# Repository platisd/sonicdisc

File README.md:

# SonicDisc
A 360° ultrasonic scanner that talks over I2C using an Atmega328P and eight HC-SR04 ultrasonic sensors.

## Overview
SonicDisc is a sensor that allows you to sense your surroundings. It utilizes 8 ultrasound sensors (HC-SR04) placed at 45° angle from each other, that can measure distances from practically every direction. It can be used in hobby-grade automotive applications, e.g. autonomous driving, obstacle detection etc or wherever quickly determining surrounding distances is relevant.

The sensor transmits the collected data over I2C and uses a separate line to signal, with a short pulse, the existence of a new set of measurements. It can be mounted on top of an Arduino UNO or used standalone. Due to the nature of the HC-SR04 sensors, the measurements can be noisy, therefore it is suggested that they are filtered. A basic Arduino example that receives and filters the incoming data can be found in [examples/SonicDiscReader](examples/SonicDiscReader).

You can find the software running on the SonicDisc in [firmware/](firmware/), the PCB design in Eagle CAD format inside [hardware/](hardware/eagle) and more sample applications using the SonicDisc in [examples](examples/).

Read the story behind the module at [platis.solutions](https://platis.solutions/blog/2017/08/27/sonicdisc-360-ultrasonic-scanner/).

## How does it work
SonicDisc is comprised of an Atmega328P microcontroller that triggers all the ultrasound sensors at the same time, receives the echo pulses via pin change interrupts and then proceeds to calculate the detected distances. The use of interrupts, in contrast to how the HC-SR04 sensors are typically utilized, enable us to conduct all measurements at the "same" time which translates into new sets of `8` measurements every `10 milliseconds`.

As an I2C slave, whenever a new set of measurements is ready to be transmitted, a short pulse is sent over the `INT` pin, prompting the master to request the data. In other words the I2C master reading the data from the SonicDisc, does not have to poll but merely wait for the indicative signal and then make the I2C request. Despite not suggested, it is possible to use SonicDisc without connecting the `INT` pin to an interrupt, however the master will not be able to assure the existence of a new data.

## How to connect
| SonicDisc | Host MCU  |
| :----:    |:----:     |
| VCC       |  5V       |
| GND       |  GND      |
| SDA       |  SDA      |
| SCL       |  SCL      |
| INT       |  ISR      |

If you are mounting the SonicDisc on top of an Arduino UNO as a shield, you only have to (optionally but suggested) connect the `INT` signal to an ISR pin.

## I2C protocol
SonicDisc communicates using the I2C bus as a slave, meaning that it receives data from a master and responds to data requests.

### Address
SonicDisc's I2C address is currently hardcoded to `0x09`.

### Set operational state
SonicDisc has two operational states between which you can switch.

| **Action**                    | **Byte to send**  | **Notes**                                   |
| :-----------:                 |:-------------:    | :----:                                      |
| Set state to `STANDBY`        | 0x0A              | SonicDisc's initial state                   |
| Set state to `MEASURING`      | 0x0B              | Set to this state to start the measurements |

**Arduino example:**
```arduino
Wire.beginTransmission(0x09);
Wire.write(0x0B); // Instruct SonicDisc to start measuring
Wire.endTransmission(0x09);
```
### Get data
SonicDisc responds to I2C requests with packages of `9` bytes that include an error code and sensor measurements. A typical package structure is described below.

Regarding the error codes, when the first byte is a `0` then everything went well and the trailing measurements are valid. If it is `1`, it means that this set of data has already been transmitted and a measurement is currently under way. You will encounter this if you poll the sensor fast enough, without taking into consideration the `INT` signal which indicates SonicDisc is ready to transmit new data. Finally, `2` designates that the module is in standby state and no measurements are being conducted.

| **Byte Index** | **Range** | **Purpose** | **Notes**                                                               |
| :----:         |:----:   | :----:        | :----:                                                                  |
| 0              |  0-2    | Error code    | **0**: No error, **1**: Incomplete measurement, **2**: In standby state |
| 1              |  0-255  | Ultrasonic 0  | **0**: Error in measurement, **1**: TBD, **2-255**: Valid distance (cm) |
| 2              |  0-255  | Ultrasonic 1  | **0**: Error in measurement, **1**: TBD, **2-255**: Valid distance (cm) |
| 3              |  0-255  | Ultrasonic 2  | **0**: Error in measurement, **1**: TBD, **2-255**: Valid distance (cm) |
| 4              |  0-255  | Ultrasonic 3  | **0**: Error in measurement, **1**: TBD, **2-255**: Valid distance (cm) |
| 5              |  0-255  | Ultrasonic 4  | **0**: Error in measurement, **1**: TBD, **2-255**: Valid distance (cm) |
| 6              |  0-255  | Ultrasonic 5  | **0**: Error in measurement, **1**: TBD, **2-255**: Valid distance (cm) |
| 7              |  0-255  | Ultrasonic 6  | **0**: Error in measurement, **1**: TBD, **2-255**: Valid distance (cm) |
| 8              |  0-255  | Ultrasonic 7  | **0**: Error in measurement, **1**: TBD, **2-255**: Valid distance (cm) |

**Arduino example:**

```arduino
const unsigned int PACKET_SIZE = 9;
unsigned int packet[PACKET_SIZE] = {0};
unsigned int packetIndex = 0;
Wire.requestFrom(0x09, PACKET_SIZE);
while (Wire.available() && packetIndex < PACKET_SIZE) {
    i2cInput[packetIndex++] = Wire.read();
}
// Now the packet[] array holds the incoming data from SonicDisc
```

## Build one yourself
Below you can find the necessary components to build a SonicDisc yourself:

* [SonicDisc PCB](https://www.pcbway.com/project/shareproject/SonicDisc___A_360__ultrasonic_scanner__rev_1_.html)
* 8 x HC-SR04
* 1 x Atmega328P-PU
* 2 x 22pF capacitors
* 3 x 0.1uF capacitors
* 1 x 1206 LED
* 1 x 1206 220Ω resistor
* 3 x 4.7KΩ resistor
* 1 x 5-pin header
* 1 x 4-pin header
* 1 x tactile switch
* 1 x 16MHz oscillator
* 1 x ISCP pin header
* 1 x 10-pin stackable header
* 2 x 8-pin stackable header
* 1 x 6-pin stackable header

## Derivative works
* [Arduino Pro Mini version with single plane sensors](https://github.com/richardFirth/sonicdisc) by [richardFirth](https://github.com/richardFirth).

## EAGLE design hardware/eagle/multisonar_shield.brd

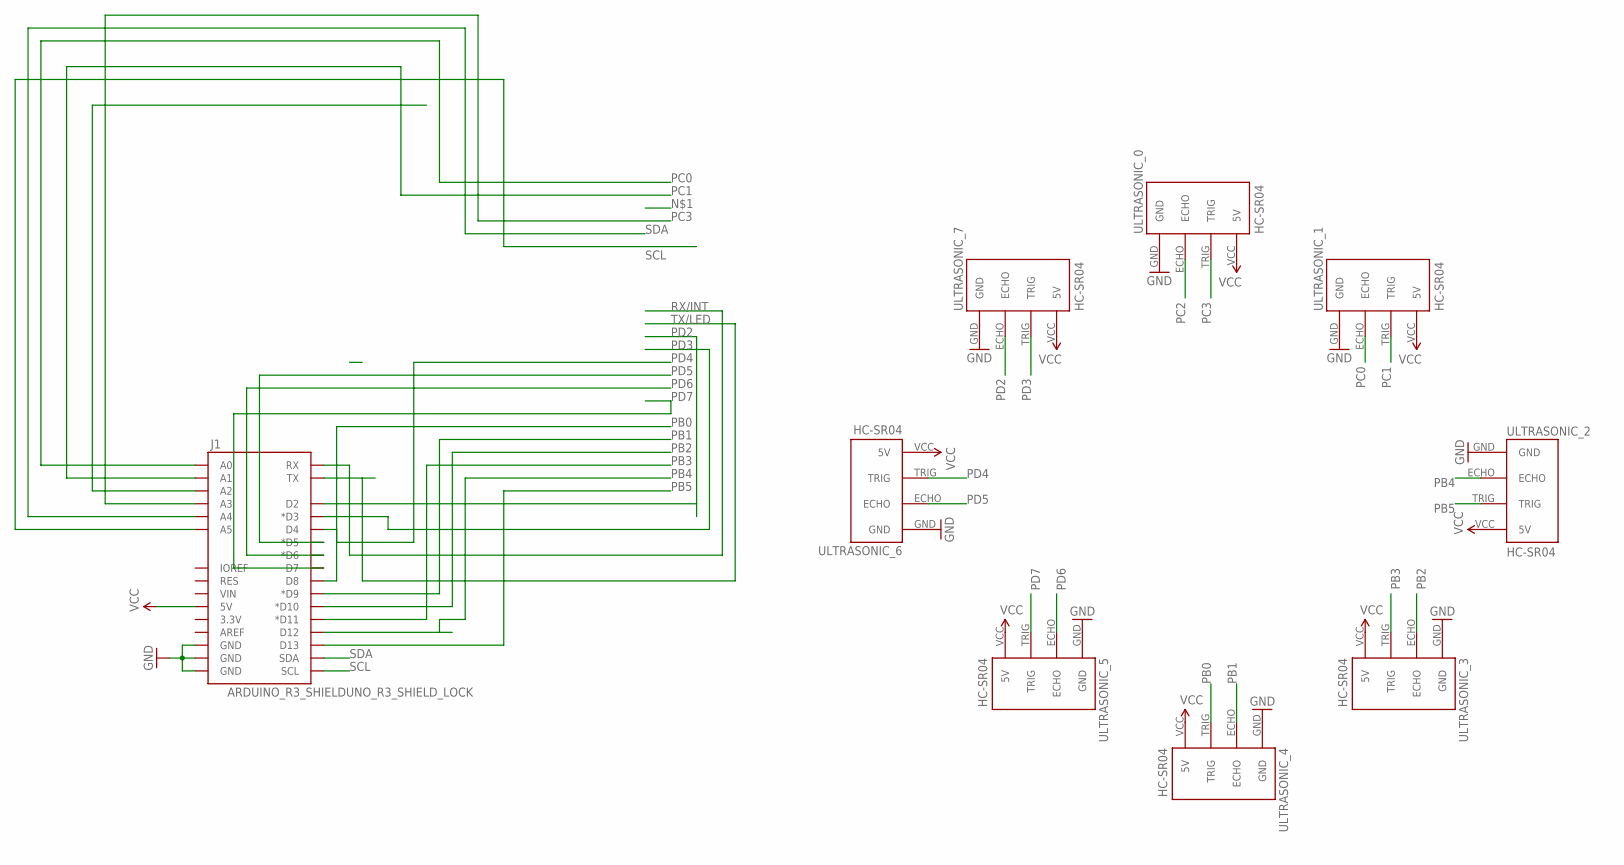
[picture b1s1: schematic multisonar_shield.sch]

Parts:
J1: ARDUINO_R3_SHIELDUNO_R3_SHIELD_LOCK; UNO_R3_SHIELD_LOCK
ULTRASONIC_0, ULTRASONIC_1, ULTRASONIC_2, ULTRASONIC_3, ULTRASONIC_4, ULTRASONIC_5, ULTRASONIC_6, ULTRASONIC_7: HC-SR04; HC-SR04_FOOTPRINT

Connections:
GND: J1.GND@0 (GND), J1.GND@1 (GND), J1.GND@2 (GND), ULTRASONIC_0.GND, ULTRASONIC_1.GND, ULTRASONIC_2.GND, ULTRASONIC_3.GND, ULTRASONIC_4.GND, ULTRASONIC_5.GND, ULTRASONIC_6.GND, ULTRASONIC_7.GND
PB0: J1.D8, ULTRASONIC_4.TRIG
PB1: J1.D9 (*D9), ULTRASONIC_4.ECHO
PB2: J1.D10 (*D10), ULTRASONIC_3.ECHO
PB3: J1.D11 (*D11), ULTRASONIC_3.TRIG
PB4: J1.D12, ULTRASONIC_2.ECHO
PB5: J1.D13, ULTRASONIC_2.TRIG
PC0: J1.A0, ULTRASONIC_1.ECHO
PC1: J1.A1, ULTRASONIC_1.TRIG
PC2: J1.A2, ULTRASONIC_0.ECHO
PC3: J1.A3, ULTRASONIC_0.TRIG
PD2: J1.D2, ULTRASONIC_7.ECHO
PD3: J1.D3 (*D3), ULTRASONIC_7.TRIG
PD4: J1.D4, ULTRASONIC_6.TRIG
PD5: J1.D5 (*D5), ULTRASONIC_6.ECHO
PD6: J1.D6 (*D6), ULTRASONIC_5.ECHO
PD7: J1.D7, ULTRASONIC_5.TRIG
RX/INT: J1.RX
SCL: J1.A5, J1.SCL
SDA: J1.A4, J1.SDA
TX/LED: J1.TX
VCC: J1.5V, ULTRASONIC_0.VCC (5V), ULTRASONIC_1.VCC (5V), ULTRASONIC_2.VCC (5V), ULTRASONIC_3.VCC (5V), ULTRASONIC_4.VCC (5V), ULTRASONIC_5.VCC (5V), ULTRASONIC_6.VCC (5V), ULTRASONIC_7.VCC (5V)

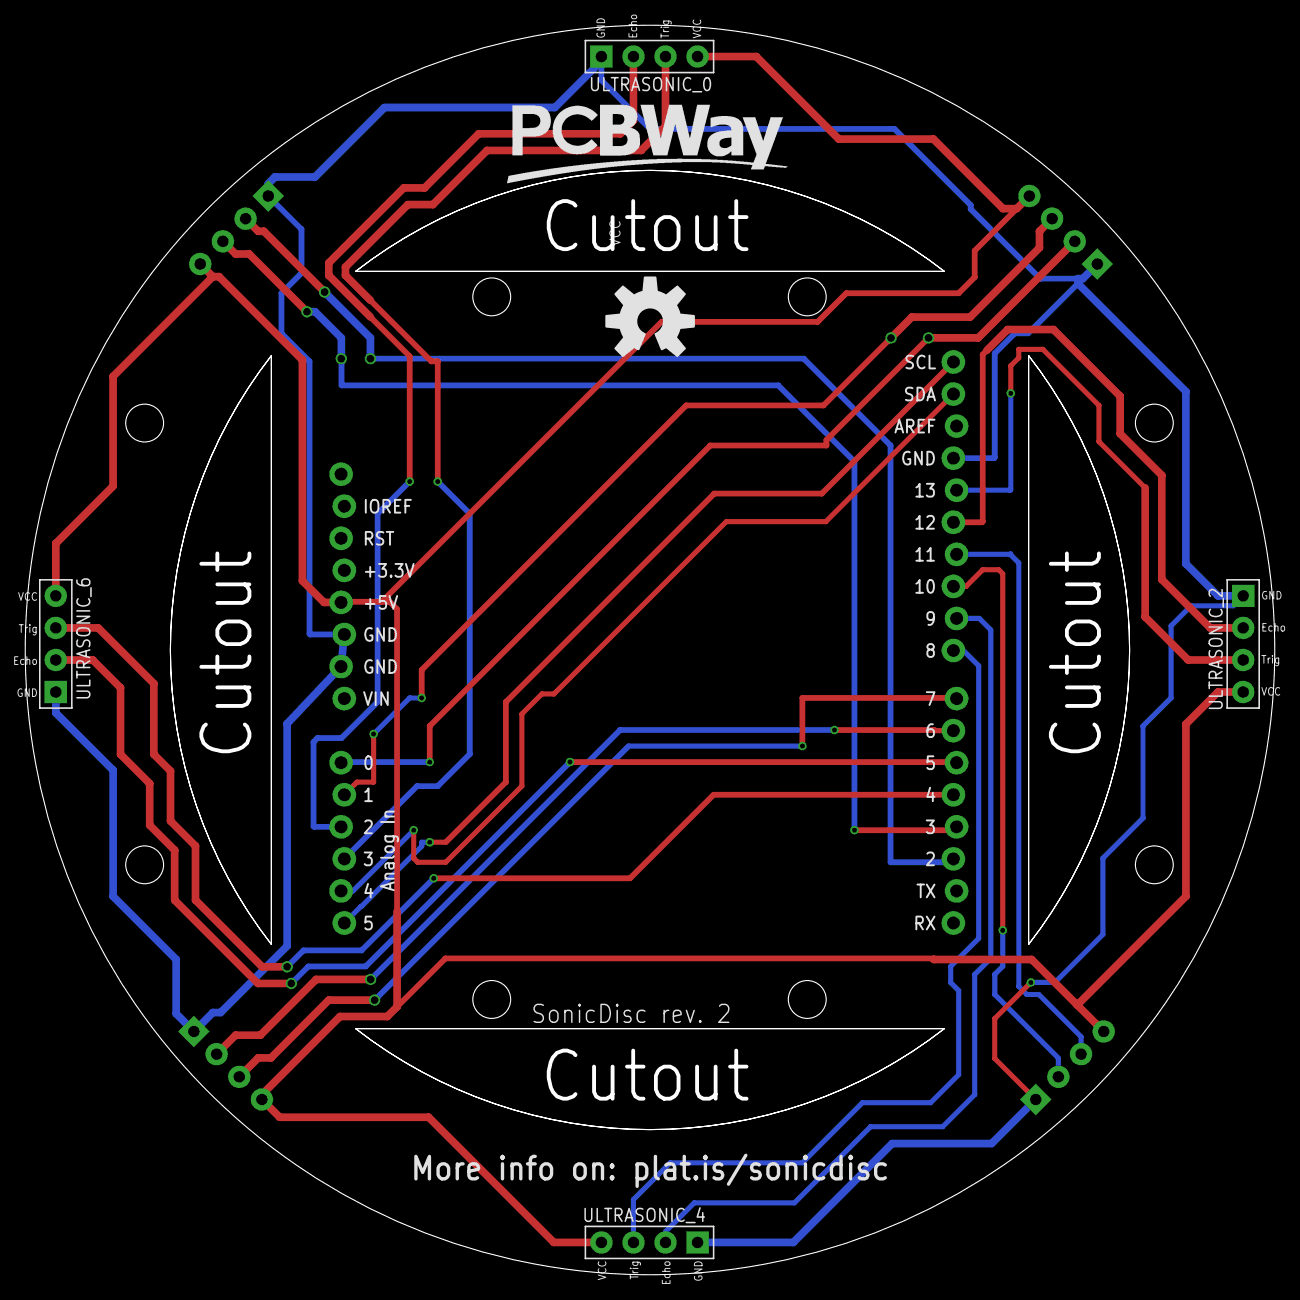
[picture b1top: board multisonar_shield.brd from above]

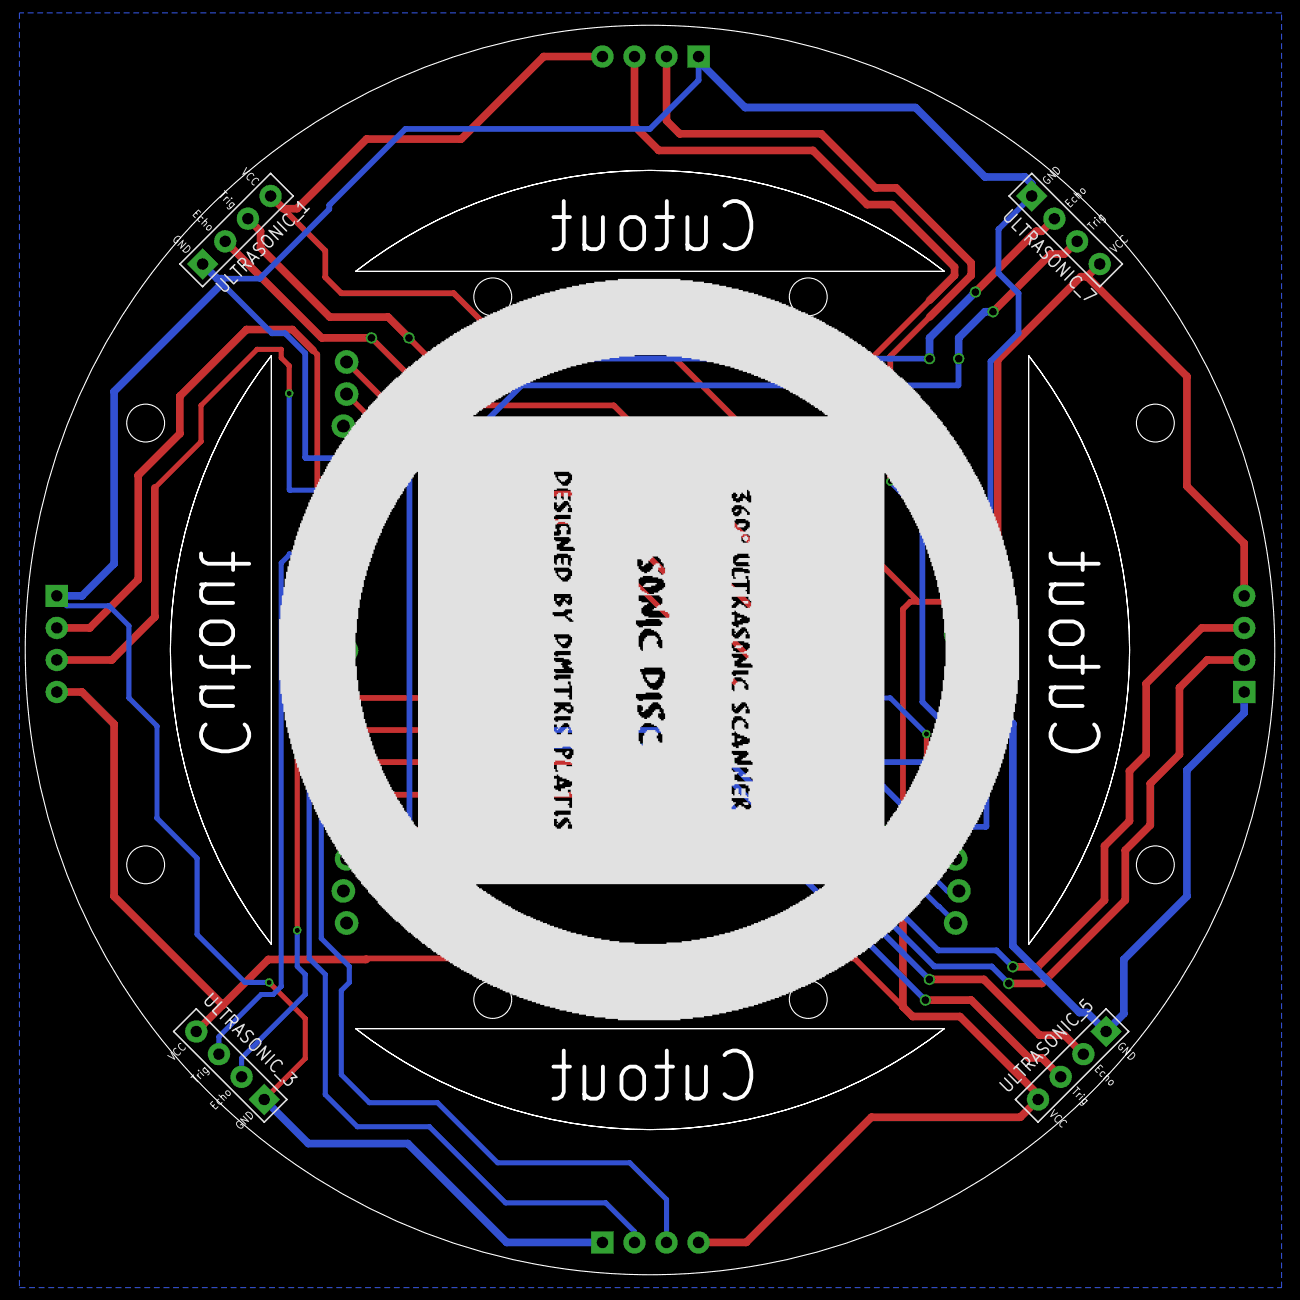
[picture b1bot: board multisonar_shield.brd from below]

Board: 2 copper layers, 99.0 x 99.0 mm, 10 parts (4 on the bottom side), 20 nets.

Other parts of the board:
U$1: OSHW-LOGO-L

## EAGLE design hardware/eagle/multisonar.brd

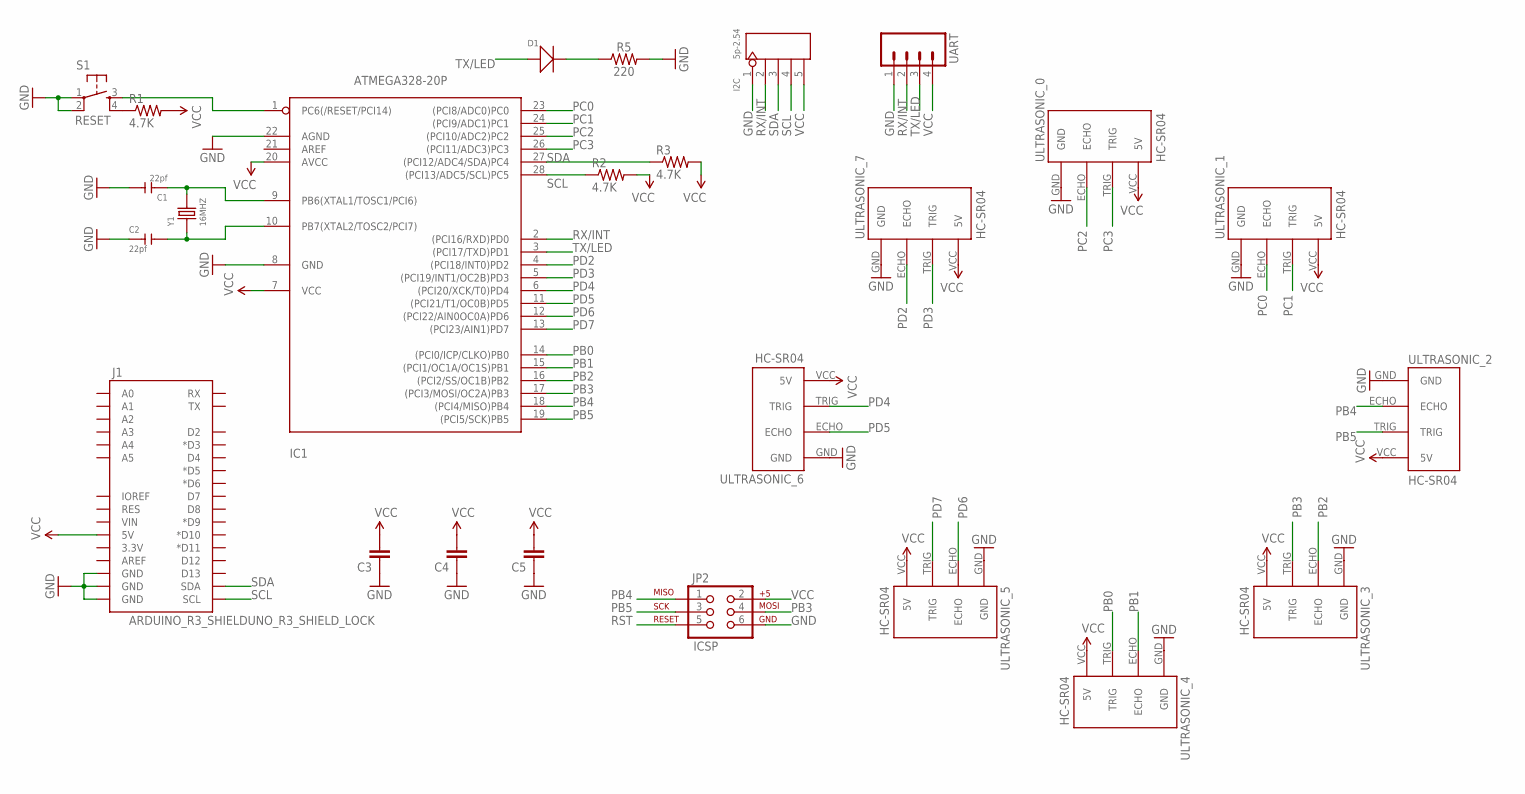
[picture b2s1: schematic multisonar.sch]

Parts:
C1, C2: 22pf; CERAMIC-2.54
C3, C4, C5: 0.1UF-50V-20%(PTH)KIT-EZ; CAP-PTH-SMALL-KIT
D1: DIODE'1206'; SOD-123
I2C: 5p-2.54; H5-2.54
IC1: ATMEGA328-20P; DIL28-3
J1: ARDUINO_R3_SHIELDUNO_R3_SHIELD_LOCK; UNO_R3_SHIELD_LOCK
JP2: ICSP; 2X3_LOCK
R1, R2, R3: 4.7K; AXIAL-0.3EZ
R5: 220; 1206
S1: RESET; TAC-SWITCH-PTH
UART: M04PTH; 1X04
ULTRASONIC_0, ULTRASONIC_1, ULTRASONIC_2, ULTRASONIC_3, ULTRASONIC_4, ULTRASONIC_5, ULTRASONIC_6, ULTRASONIC_7: HC-SR04; HC-SR04_FOOTPRINT
Y1: 16MHZ; HC49US

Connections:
GND: C1.2, C2.1, C3.1, C4.1, C5.1, I2C.1, IC1.8 (GND), IC1.22 (AGND), J1.GND@0 (GND), J1.GND@1 (GND), J1.GND@2 (GND), JP2.6, R5.2, S1.1, S1.2, UART.1, ULTRASONIC_0.GND, ULTRASONIC_1.GND, ULTRASONIC_2.GND, ULTRASONIC_3.GND, ULTRASONIC_4.GND, ULTRASONIC_5.GND, ULTRASONIC_6.GND, ULTRASONIC_7.GND
unnamed: R1.P$1 (1), S1.4
unnamed: D1.-, R5.1
unnamed: C1.1, IC1.9 (PB6(XTAL1/TOSC1/PCI6)), Y1.2
unnamed: C2.2, IC1.10 (PB7(XTAL2/TOSC2/PCI7)), Y1.1
PB0: IC1.14 ((PCI0/ICP/CLKO)PB0), ULTRASONIC_4.TRIG
PB1: IC1.15 ((PCI1/OC1A/OC1S)PB1), ULTRASONIC_4.ECHO
PB2: IC1.16 ((PCI2/SS/OC1B)PB2), ULTRASONIC_3.ECHO
PB3: IC1.17 ((PCI3/MOSI/OC2A)PB3), JP2.4, ULTRASONIC_3.TRIG
PB4: IC1.18 ((PCI4/MISO)PB4), JP2.1, ULTRASONIC_2.ECHO
PB5: IC1.19 ((PCI5/SCK)PB5), JP2.3, ULTRASONIC_2.TRIG
PC0: IC1.23 ((PCI8/ADC0)PC0), ULTRASONIC_1.ECHO
PC1: IC1.24 ((PCI9/ADC1)PC1), ULTRASONIC_1.TRIG
PC2: IC1.25 ((PCI10/ADC2)PC2), ULTRASONIC_0.ECHO
PC3: IC1.26 ((PCI11/ADC3)PC3), ULTRASONIC_0.TRIG
PD2: IC1.4 ((PCI18/INT0)PD2), ULTRASONIC_7.ECHO
PD3: IC1.5 ((PCI19/INT1/OC2B)PD3), ULTRASONIC_7.TRIG
PD4: IC1.6 ((PCI20/XCK/T0)PD4), ULTRASONIC_6.TRIG
PD5: IC1.11 ((PCI21/T1/OC0B)PD5), ULTRASONIC_6.ECHO
PD6: IC1.12 ((PCI22/AIN0OC0A)PD6), ULTRASONIC_5.ECHO
PD7: IC1.13 ((PCI23/AIN1)PD7), ULTRASONIC_5.TRIG
RST: IC1.1 (PC6(/RESET/PCI14)), JP2.5, S1.3
RX/INT: I2C.2, IC1.2 ((PCI16/RXD)PD0), UART.2
SCL: I2C.4, IC1.28 ((PCI13/ADC5/SCL)PC5), J1.SCL, R2.P$1 (1)
SDA: I2C.3, IC1.27 ((PCI12/ADC4/SDA)PC4), J1.SDA, R3.P$1 (1)
TX/LED: D1.+, IC1.3 ((PCI17/TXD)PD1), UART.3
VCC: C3.2, C4.2, C5.2, I2C.5, IC1.7 (VCC), IC1.20 (AVCC), J1.5V, JP2.2, R1.P$2 (2), R2.P$2 (2), R3.P$2 (2), UART.4, ULTRASONIC_0.VCC (5V), ULTRASONIC_1.VCC (5V), ULTRASONIC_2.VCC (5V), ULTRASONIC_3.VCC (5V), ULTRASONIC_4.VCC (5V), ULTRASONIC_5.VCC (5V), ULTRASONIC_6.VCC (5V), ULTRASONIC_7.VCC (5V)

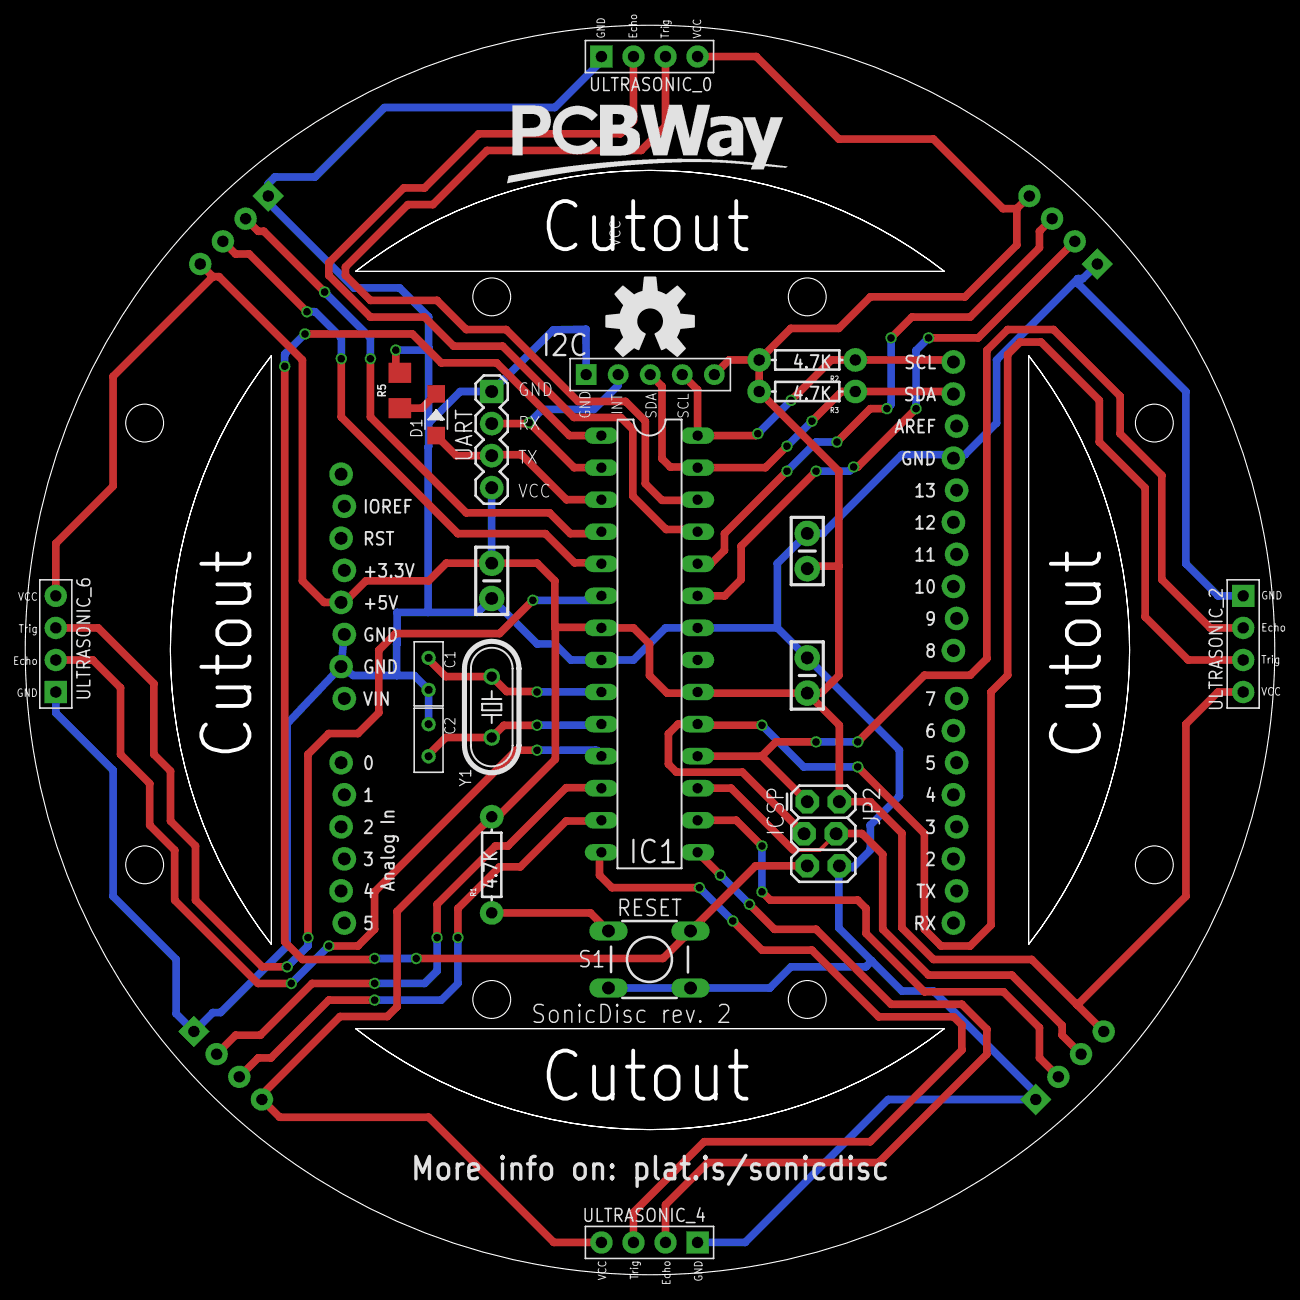
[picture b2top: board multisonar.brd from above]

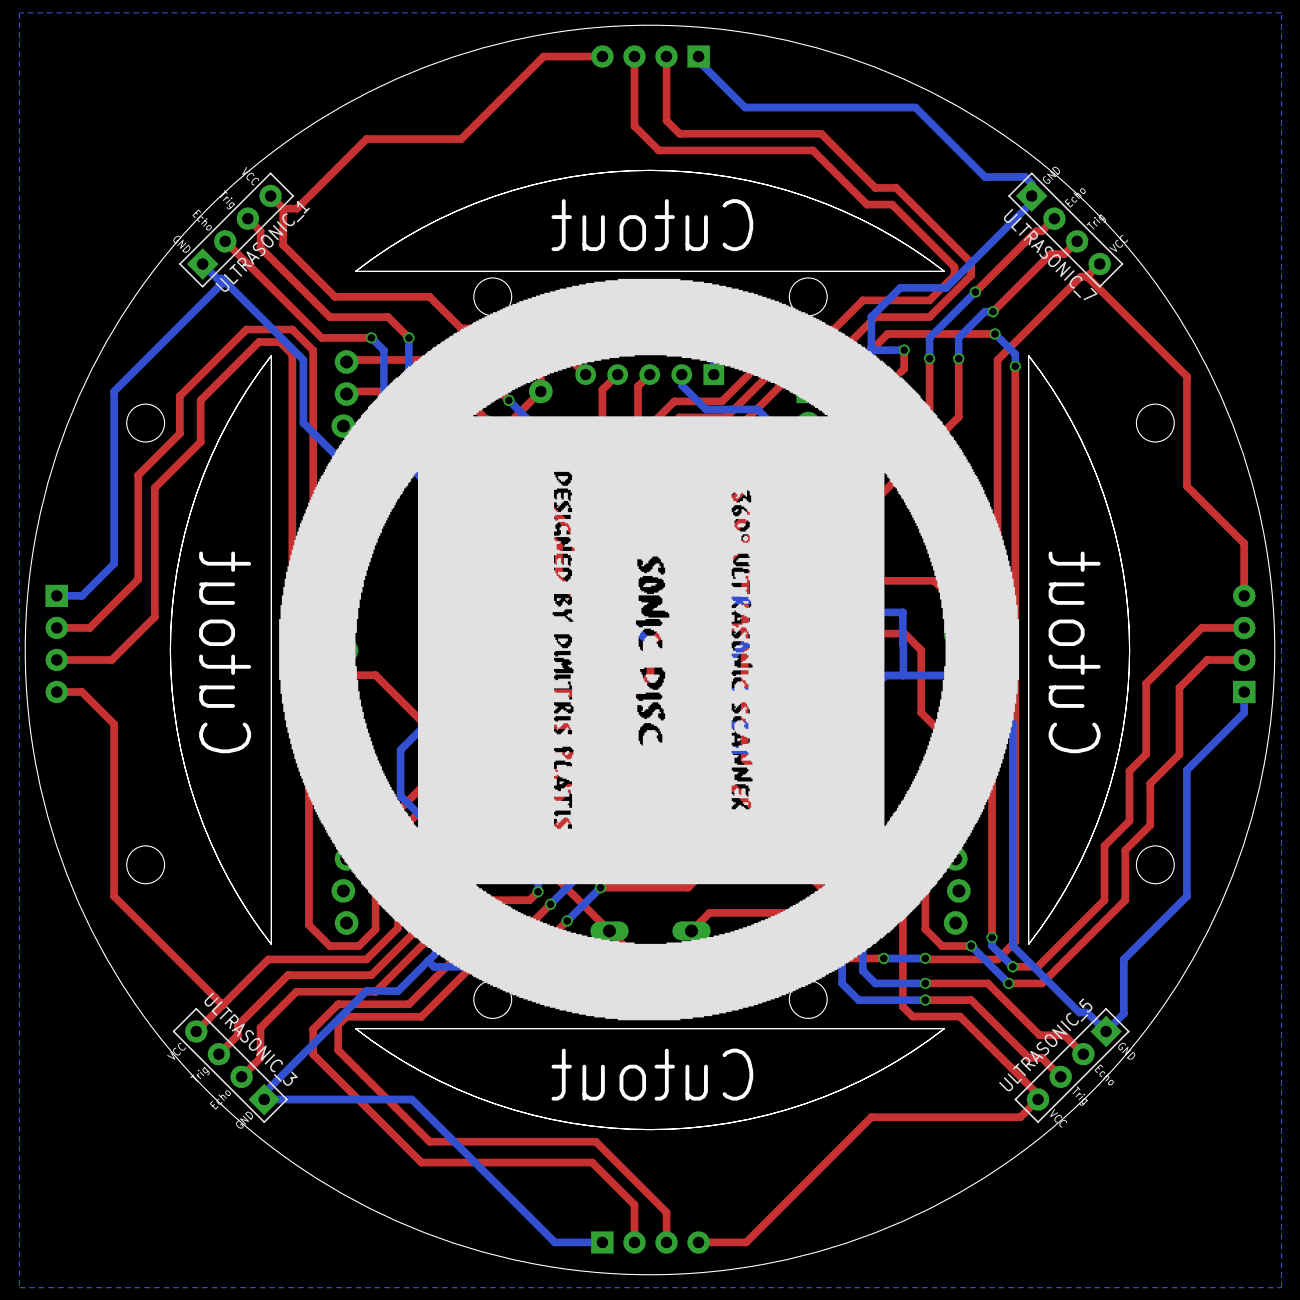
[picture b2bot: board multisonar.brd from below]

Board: 2 copper layers, 99.0 x 99.0 mm, 26 parts (4 on the bottom side), 27 nets.

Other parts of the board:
U$1: OSHW-LOGO-L

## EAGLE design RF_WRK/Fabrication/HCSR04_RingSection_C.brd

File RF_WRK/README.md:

# Richard Version

*I wasn't sure how to add this to the inital repo, so I put my stuff in this folder so as not to mess up however your stuff is organized.*

Stuff:

**SonicDiscReader_B** - this is pretty much identical to your original code, except the output is parsed to interact with my processing file

**SonDisk_Proc3** - this is a visual display of the outputs from sonicDiskReader_B written in processing3.

**Fabrication** contains eagle PCB fabrication files, as well as laser cutter files to make the acrylic holder plate thing.

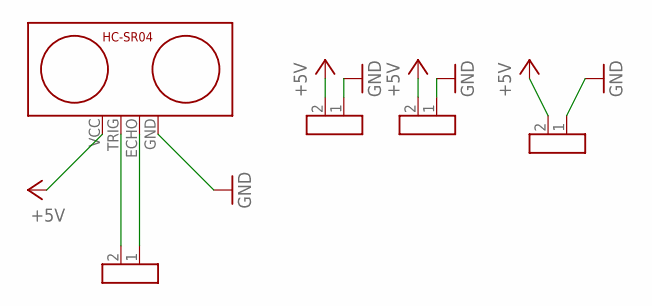
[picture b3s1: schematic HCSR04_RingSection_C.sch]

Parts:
U$1: HCSR04
U$2, U$3, U$4, U$6: 2XHEADER

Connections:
+5V: U$1.VCC, U$2.2, U$3.2, U$6.2
ECHO: U$1.ECHO, U$4.1
GND: U$1.GND, U$2.1, U$3.1, U$6.1
TRIG: U$1.TRIG, U$4.2

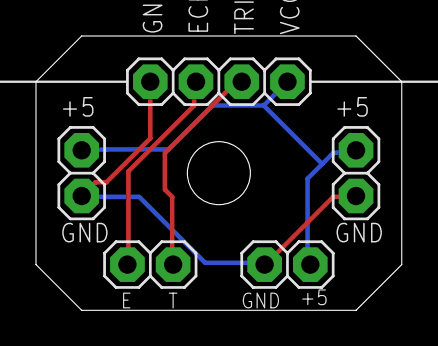
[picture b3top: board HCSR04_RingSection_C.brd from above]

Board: 2 copper layers, 20.3 x 15.2 mm, 6 parts (0 on the bottom side), 4 nets.

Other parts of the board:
U$5: 632

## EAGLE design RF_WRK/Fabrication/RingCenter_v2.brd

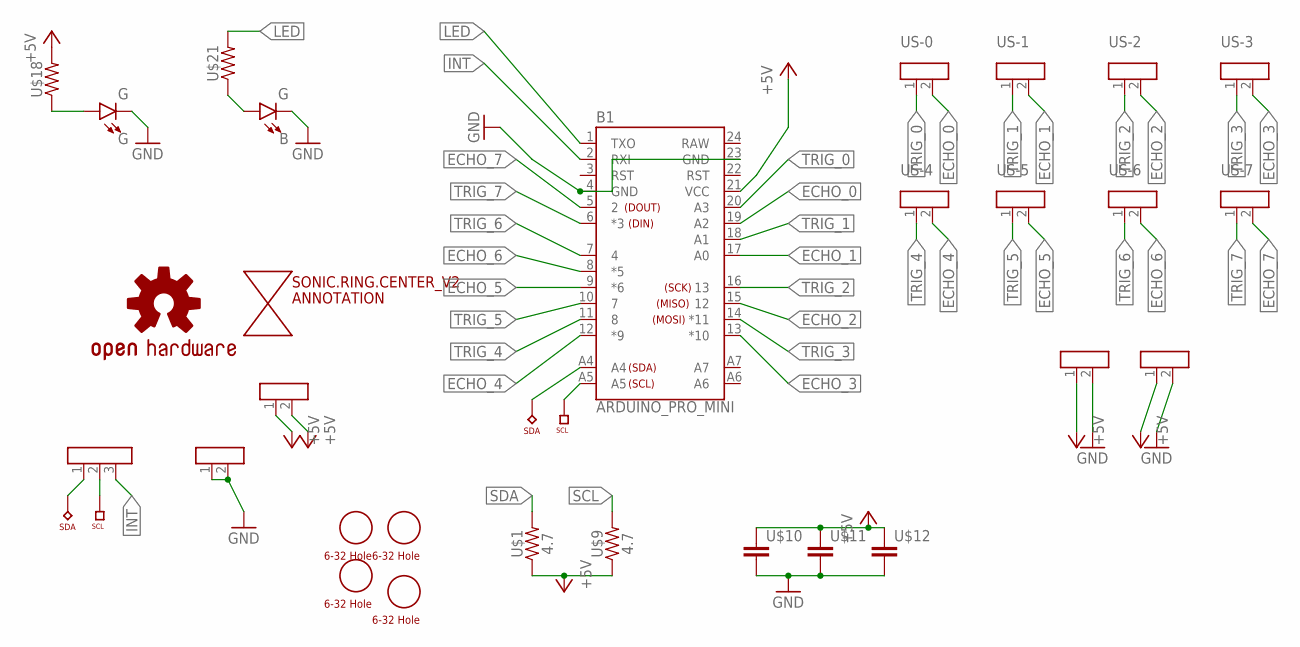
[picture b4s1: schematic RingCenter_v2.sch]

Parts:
B: G; LED_SMD
B1: ARDUINO_PRO_MINI
G: G; LED_SMD
LOGO1: OSHW-LOGOM; OSHW-LOGO-M
SONIC.RING.CENTER_V2: ANNOTATION
U$1, U$9: 4.7; R1206
U$2, U$3, U$4, U$5, U$6, U$7, U$8: 2XHEADER
U$10, U$11, U$12: CAP_SMCAP; C1206
U$13, U$14, U$15, U$16: 632
U$17: 3XHEADER
U$18, U$21: RESISTORSMD; R1206
US-0, US-1, US-4, US-5, US-6: 2XHEADER

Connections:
+5V: B1.21 (VCC), U$1.1, U$9.1, U$10.1, U$11.1, U$12.1, U$18.2, US-4.1, US-5.1, US-6.1, US-6.2
ECHO_0: B1.19 (A2), US-0.2
ECHO_1: B1.17 (A0), U$8.2
ECHO_2: B1.15 (12), U$2.2
ECHO_3: B1.13 (*10), U$7.2
ECHO_4: B1.12 (*9), U$3.2
ECHO_5: B1.9 (*6), U$6.2
ECHO_6: B1.8 (*5), U$4.2
ECHO_7: B1.5 (2), U$5.2
GND: B.C, B1.4 (GND), B1.23 (GND), G.C, U$10.2, U$11.2, U$12.2, US-1.1, US-1.2, US-4.2, US-5.2
INT: B1.2 (RXI), U$17.3
LED: B1.1 (TXO), U$21.2
unnamed: G.A, U$18.1
unnamed: B.A, U$21.1
RAW: B1.24 (RAW)
SCL: B1.A5, U$9.2, U$17.2
SDA: B1.A4, U$1.2, U$17.1
TRIG_0: B1.20 (A3), US-0.1
TRIG_1: B1.18 (A1), U$8.1
TRIG_2: B1.16 (13), U$2.1
TRIG_3: B1.14 (*11), U$7.1
TRIG_4: B1.11 (8), U$3.1
TRIG_5: B1.10 (7), U$6.1
TRIG_6: B1.7 (4), U$4.1
TRIG_7: B1.6 (*3), U$5.1

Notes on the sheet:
US-0
US-1
US-2
US-3
US-5
US-4
US-6
US-7

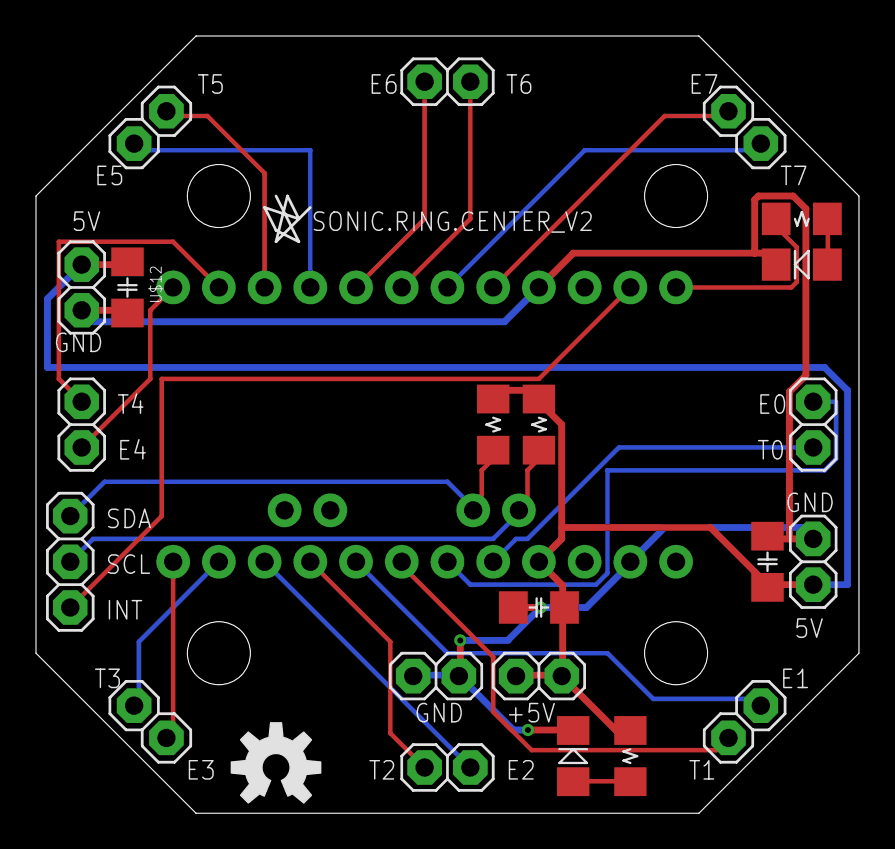
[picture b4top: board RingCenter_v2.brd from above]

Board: 2 copper layers, 45.7 x 43.2 mm, 29 parts (0 on the bottom side), 24 nets.

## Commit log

2017-08-21 Add calculation, reset and getdistance methods
2017-08-21 Add bottom silk screen
    Board Rev. 0, sent to PCBWay
2017-08-21 Routed all components
    TO-DO: Add silk screen
2017-08-21 Add pin numbers (not Arduino-like)
2017-08-21 Send pulse upon completing a measurement
    Also increase the duration of a measurement to 15ms
2017-08-21 Add initial Sonic Sensor implementation
2017-08-21 Corrected handling of measurements according to datasheet
    TO-DO: Narrow down the sensors to check inside the interrupts
    depending on which vector the interrupt is coming from
2017-08-21 Prepare and start new measurements while calculating the previous ones
2017-08-21 Use the non volatile copy and constrain larger results
2017-08-21 Add prepare to calculate and reset echo
    To be used inside critical sections
2017-08-21 New project structure and added components
2017-08-21 Compose the package to send via i2c
2017-08-21 Check only specific sensors for echo pulse
    Depending on which interrupt vector was triggered
2017-08-21 Add initialization of member variables
2017-08-21 Handle the echo inside an interrupt
    However, just realized that this is not the way that the SR04 works. The duration of the echo PULSE should be measured instead.
    Also, set the trigger pins low for a few microseconds before sending the pulse.
2017-08-21 Changed method names to reveal less details, add methods to finish measurement
    TO-DO: Calculate distance
2017-08-21 Add triggering all sensors via port manipulation
2017-08-21 Change IRQ to INT for clarity
    It should be easier to explain to novice users
2017-08-21 Increase measurement frequency
    Since filtering will be done on the reader side,
    let's keep this fast enough.
2017-08-21 Get cleaner trigger pulse
    By setting the pins briefly LOW first
2017-08-21 Add initial control logic for measurements
    TO-DO: Trigger all sensors at once via port manipulation
2017-08-21 Add Arduino-like pins
2017-08-21 Add initial I2C interface
2017-08-21 Add include so to compile correctly
2017-08-21 Routed power lines
2017-08-21 Add ultrasonic sensors
2017-08-21 Add states, error codes and i2c receipts
2017-08-21 Initial files with dimension layer
2017-08-21 Setup change interrupt method
    Used example from https://playground.arduino.cc/Main/PinChangeInterrupt
2017-08-21 Increased spacing between components
2017-08-21 Add initial firmware
2017-08-21 Added milling layer
2017-08-21 Add blinking according to state
2017-08-21 Moved firmware folder to repo root
2017-08-21 Add Sonic Reader example
2017-08-22 Add filtering to the incoming values
    The filter will read the specified amount of measurements
    from each sensor and then will determine whether the variance
    is too high for the measurements to be valid.
2017-08-22 Add readme to SonicDiscReader sample sketch
2017-08-22 Reset sensors when going back to standby
2017-08-22 Add gitattributes
    Ignore eagle and other hardware related files
2017-08-22 Add README for firmware
2017-08-23 Small refactoring when handling filtered measurements
    For better readability
2017-08-23 Add project-level readme
2017-08-24 Removed hardcoded packet size
    Also added default packet size for better usability with
    most common scenarios.
2017-08-24 Describe communication protocol
2017-08-26 Add an object follower example with a Smartcar
2017-08-26 Initial Smartcar Parker commit
    Including preliminary statemachine
2017-08-26 Add general parking concept
2017-08-26 Finalize Smartcar parker
    Working example that can park the car in
    gaps of various lengths.
2017-08-27 Add youtube link
2017-08-27 Explain better what error codes stand for
2017-08-28 Add link to blog article
2017-11-11 Use the lock package for easier soldering
    The lock arduino shield package is used to facilitate
    the headers staying in place while soldering
2017-11-11 Ultrasonic position fix
2017-11-11 Moving i2c header downwards
    So there is more space when angled headers are used
2017-11-11 Increase board size to 99mm
    Fixes #1
2017-11-11 Update link to buy rev.1 PCB
2018-01-29 added RF Folder
2018-02-04 add fabrication files, code, and assembly instructions
2018-02-04 add instructions ppt
2018-02-11 restructure folders, add Processing3 sketch
2018-02-11 rename Processing3 file, and remove newlines, commented out code
2018-02-11 update documentation in processing3
2018-02-11 Removed some unused .pde files
2018-02-17 update formating and readme
2018-02-17 update readme to have derivitive works section
2018-02-17 update readme to use md links
2018-02-17 Small formatting fix
2018-09-02 Add rev. 2 board
    * Move I2C header down for easier cabling through the cutout
    * Add OSH logo
    * Add PCBWay.com logo (sponsors)
2020-03-30 Hacky relayout to eliminate the need for a custom onboard Arduino. Is now just a regular Arduino shield
2020-03-30 Fixed a few glitches
2020-03-30 Fixed DRC errors
2020-03-30 Cosmetic tweaks
2020-04-12 Adapted for to be an Arduino shield
2020-04-30 Making it easier to graph
2020-05-01 Optimized for plotting

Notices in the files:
parts and their libraries:
SparkFun-Resistors: Licensing: Creative Commons ShareAlike 4.0 International - https://creativecommons.org/licenses/by-sa/4.0
